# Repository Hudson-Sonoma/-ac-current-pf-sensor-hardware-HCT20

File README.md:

# ac-current-pf-sensor-hardware-HCT20
I2C 50/60Hz 100 amp AC current sensor module - hardware

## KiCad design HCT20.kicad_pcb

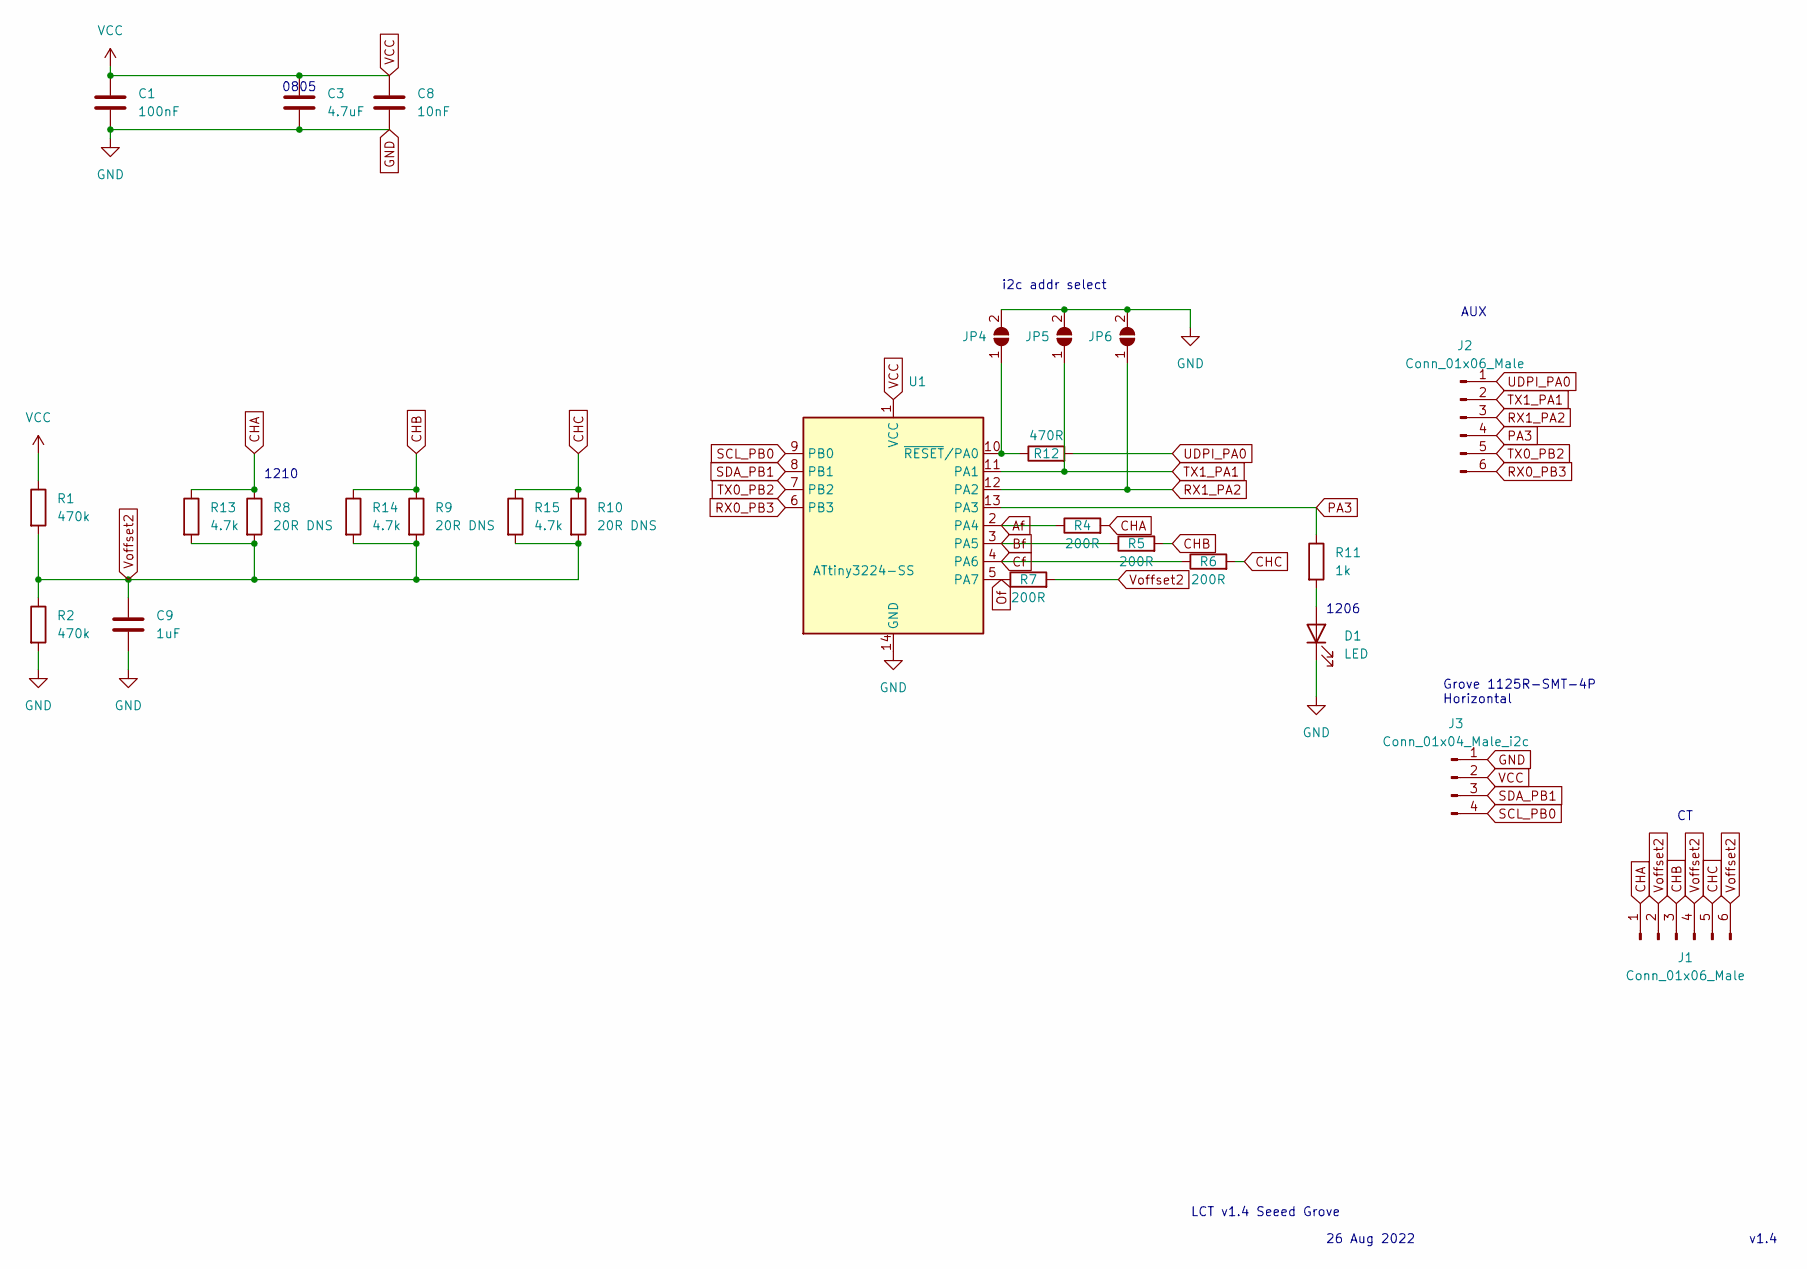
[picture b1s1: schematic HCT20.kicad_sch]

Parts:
C1: 100nF; C_0603_1608Metric
C3: 4.7uF; C_0805_2012Metric
C8: 10nF; C_0603_1608Metric
C9: 1uF; C_0805_2012Metric
D1: LED; LED_0805_2012Metric
J1, J2: Conn_01x06_Male; TerminalBlock_TE_282834-6_1x06_P2.54mm_Horizontal
J3: Conn_01x04_Male_i2c; JST_PH_S4B-PH-SM4-TB_1x04-1MP_P2.00mm_Horizontal
JP4, JP5, JP6: SolderJumper_2_Open; SolderJumper-2_P1.3mm_Open_TrianglePad1.0x1.5mm
R1, R2: 470k; R_0603_1608Metric
R4, R5, R6, R7: 200R; R_0603_1608Metric
R8, R9, R10: 20R DNS; R_1210_3225Metric
R11: 1k; R_0603_1608Metric
R12: 470R; R_0603_1608Metric
R13, R14, R15: 4.7k; R_0603_1608Metric
U1: ATtiny3224-SS; SOIC-14_3.9x8.7mm_P1.27mm

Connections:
Af: R4.1, U1.2 (PA4)
Bf: R5.1, U1.3 (PA5)
CHA: J1.1, R4.2, R8.1, R13.1
CHB: J1.3, R5.2, R9.1, R14.1
CHC: J1.5, R6.2, R10.1, R15.1
Cf: R6.1, U1.4 (PA6)
GND: C1.2, C3.2, C8.2, C9.2, D1.1 (K), J3.1, JP4.2 (B), JP5.2 (B), JP6.2 (B), R2.2, U1.14 (GND)
unnamed: D1.2 (A), R11.2
unnamed: JP4.1 (A), R12.1, U1.10 (~RESET/PA0)
Of: R7.1, U1.5 (PA7)
PA3: J2.4, R11.1, U1.13 (PA3)
RX0_PB3: J2.6, U1.6 (PB3)
RX1_PA2: J2.3, JP6.1 (A), U1.12 (PA2)
SCL_PB0: J3.4, U1.9 (PB0)
SDA_PB1: J3.3, U1.8 (PB1)
TX0_PB2: J2.5, U1.7 (PB2)
TX1_PA1: J2.2, JP5.1 (A), U1.11 (PA1)
UDPI_PA0: J2.1, R12.2
VCC: C1.1, C3.1, C8.1, J3.2, R1.1, U1.1 (VCC)
Voffset2: C9.1, J1.2, J1.4, J1.6, R1.2, R2.1, R7.2, R8.2, R9.2, R10.2, R13.2, R14.2, R15.2

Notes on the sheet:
i2c addr select
v1.4
26 Aug 2022
LCT v1.4 Seeed Grove
0805
1206
AUX
Grove 1125R-SMT-4P Horizontal
1210

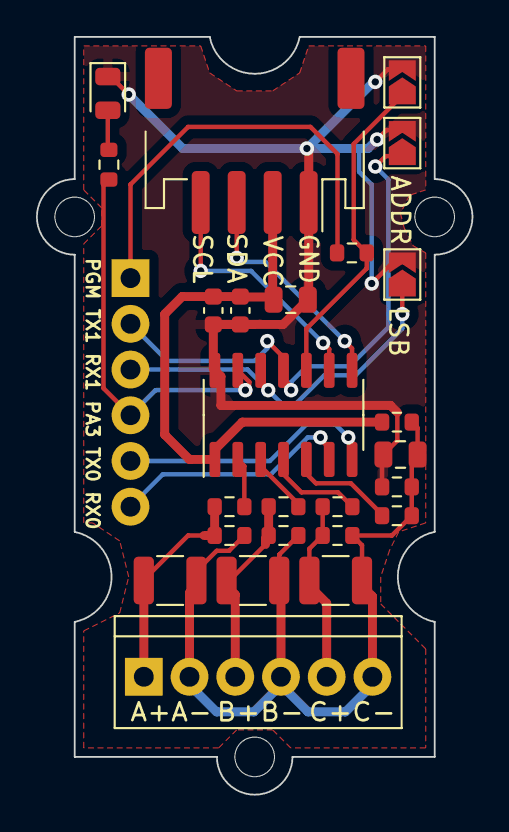
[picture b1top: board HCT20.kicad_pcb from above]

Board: 2 copper layers, 24.2 x 42.1 mm, 26 parts (0 on the bottom side), 20 nets.

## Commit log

2023-06-01 initial
2023-06-01 Update README.md
    add images
